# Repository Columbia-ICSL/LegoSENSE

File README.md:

# LegoSENSE
LegoSENSE makes building and deploying sensing systems as easy and as fast as building legos, for **everyone**. LegoSENSE is a software & hardware framework for rapid sensor deployments.

We have provided detailed documentation (and instructional videos soon), for both users, and developers looking to expand the ecosystem.

## Getting Started

For general users, if your system did not come with the software, please flash our prebuilt Raspberry Pi image to the SD card and plug in the hardware.

To develop or build the system from source, please clone this repository using the following git commands. Make sure to pass the `--recurse-submodules` flag to the clone command.

```bash
git clone --recurse-submodules git@github.com:Columbia-ICSL/LegoSENSE.git
```

`/software` contains the source code for LegoSENSE's software system running on Raspberry Pi.

`/hardware` contains all the design resources for developing hardware modules for LegoSENSE, including instructions, hardware references, and design templates.

## Citation

If your academic work has used LegoSENSE, please cite our paper below.

> Minghui Zhao, Stephen Xia, Jingping Nie, Kaiyuan Hou, Avik Dhupar, and Xiaofan Jiang. 2023. LegoSENSE: An Open and Modular Sensing Platform for Rapidly-Deployable IoT Applications. In International Conference on Internet-of-Things Design and Implementation (IoTDI '23), May 09--12, 2023, San Antonio, TX, USA. ACM, New York, NY, USA 14 Pages. [https://doi.org/10.1145/3576842.3582369](https://doi.org/10.1145/3576842.3582369)

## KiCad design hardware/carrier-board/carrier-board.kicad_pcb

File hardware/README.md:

# LegoSENSE Development Guide - Hardware
*This document is written for a hardware developer audience. For information on using LegoSENSE, see [Getting Started](../README.md).*

## Getting Started: hardware design steps

### Step 1: Get Sensor to Work on Breadboard

Acquire a sensor evaluation board (breakout board) and make it work with Raspberry Pi. You may consult the sensor manufacturer for example codes and getting started guides. Once you have the sensor's driver code running on Raspberry Pi and are able to acquire data, you are ready for the next step.

### Step 2: Switch to Module Development Board

In this step, you will move the sensor circuit to a module-like development board that can be plugged into LegoSENSE's carrier board.

There are three module development boards you can use as shown below. On the top half of the board, the 21-Pin connector is broken out for soldering; on the bottom half of the board, type 1 employs a breadboard-style layout, type 2 employs a protoboard-style layout and type 3 includes the common 1.25mm JST connector and 1.0mm I2C connector (STEMMA QT / Qwiic).

| Development Board Type 1                       | Development Board Type 2                       | Development Board Type 3                       |
| ---------------------------------------------- | ---------------------------------------------- | ---------------------------------------------- |
|  |  |  |
|  |  |  |

Choose the one that's most convenient for you to work with, and move the circuit from breadboard to the development board and solder it on there.

Plug the evaluation board into carrier board. Depending on which slot you've plugged in, you will need to change the pin definitions in your sensor driver code to match the pin that the specific carrier board module slot uses. You can consult the table under [Carrier Board Bus Layout](#carrier-board-bus-layout).

Once you get the sensor driver code up running, you are ready for the next step.

### Step 3: Port code into LegoSENSE Framework

In this step, we will port the working sensor driver code into LegoSENSE's framework. Follow [Software Development Guide](../software_dev.md) - once you have the sensor driver running from LegoSENSE's software stack and see the sensor data on the dashboard, you are ready for the final step.

### Step 4: Design and Manufacture Module PCB

In this step, we will create the final version of the sensor module PCB. A template sensor module PCB project is provided in `/hardware/sensor-modules/template`.

| Template Sensor Module PCB (front)                  | Template Sensor Module PCB (back)                   |
| --------------------------------------------------- | --------------------------------------------------- |
|  |  |

1. Duplicating the module template PCB file. This template file is pre-populated with the LegoSENSE standard 21-Pin connector and a EEPROM for auto-recognition of the module. Do not edit this part.
2. Move all the sensor components and peripherials onto the bottom part of the module PCB.
3. Finish the PCB and manufacture it. You could either program the eeprom at manufacturing time and populate it with the ascii string name of the driver, or you can plug in the PCB and use `/software/src/hal/eeprom/write_eep.py` to program the eeprom.

## Project Layout

- `sensor-modules`
  - `template`
  - `<existing_module_names>`
    - `<module_name>.kicad_pro/kicad_sch/kicad_pcb`: KiCad project for the sensor module PCB
    - `jlcpcb`: Folder containing PCB fabrication files. This folder is generated by KiCad plugin [kicad-jlcpcb-tools]( https://github.com/bouni/kicad-jlcpcb-tools).
      - `gerber`: Gerber file for PCB manufacturing
      - `assembly`: Bill of materials (BOM) and parts placement position file for pick-and-place machine (POS)

- `carrier-board`: Carrier board (as a Raspberry Pi shield) PCB design and fabrication files
  - `carrier-board.kicad_pro/kicad_sch/kicad_pcb`: KiCad project for the top-level carrier board PCB
  - `<ADC/eeprom_mux/HeaderToRpi4_overlay1/level_shifter_2ch/sensor_module>.kicad_sch`: Schematics files for submodules in the carrier board PCB project
  - `jlcpcb`: Folder containing PCB fabrication files. This folder is generated by KiCad plugin [kicad-jlcpcb-tools]( https://github.com/bouni/kicad-jlcpcb-tools).
    - `gerber`: Gerber file for PCB manufacturing
    - `assembly`: Bill of materials (BOM) and parts placement position file for pick-and-place machine (POS)
- `module-development-boards`: PCB designs for three different module development boards
- `kicad-library`: Submodule linked to a separate GitHub repository containing the PCB library symbols of the components used in the hardware designs.

### Current List of PCB Design Files

#### Carrier Board PCB

| Carrier Board Front Side             | Carrier Board Back Side              |
| ------------------------------------ | ------------------------------------ |
|  |  |

#### Sensor Modules

| **M1: Temperature, Humidity, Pressure, Wind Speed** | **M2: Ambient Light Color, Light Intensity**                 | **M3: Proximity, Microphone**          | **M4: Motion (IMU)**              |
| --------------------------------------------------- | ------------------------------------------------------------ | -------------------------------------- | --------------------------------- |
|                               |                                        |                  |             |
| **M5: Thermocouple (Temperature)**                  | **M6: Particulate Matter (PM1, PM2.5, PM10); Any I2C Sensor with STEMMA QT / Qwiic** | **M7: CO2, Volatile Organic Compound** | **M8: Gas Density (MQ-X Series)** |
|                               |                                        |                  |             |

## Carrier Board Bus Layout
Note: Raspberry Pi GPIO numbering in this table are BCM (broadcom) pin numbers and is not the physical pin on Raspberry Pi board.

|            | I2C                    | SPI                             | UART (TX, RX)                      | ADC         | GPIO |
| ---------- | ---------------------- | ------------------------------- | ---------------------------------- | ----------- | ---- |
| Module 1   | I2C1 <br/>`/dev/i2c-1` | SPI0, CS0 <br/>`/dev/spidev0.0` | UART1 (14, 15) <br/>`/dev/ttyS0`   | ADC1, CH1-2 | 24   |
| Module 2   | I2C1 <br/>`/dev/i2c-1` | SPI0, CS1 <br/>`/dev/spidev0.1` | UART2 (0, 1) <br/>`/dev/ttyAMA1`   | ADC1, CH3-4 | 25   |
| Module 3   | I2C6 <br/>`/dev/i2c-6` | SPI1, CS0 <br/>`/dev/spidev1.0` | UART3 (4, 5) <br/>`/dev/ttyAMA2`   | ADC2, CH1-2 | 26   |
| Module 4   | I2C6 <br/>`/dev/i2c-6` | SPI1, CS1 <br/>`/dev/spidev1.1` | UART5 (12, 13) <br/>`/dev/ttyAMA3` | ADC2, CH3-4 | 27   |
| ADC1       | I2C1, addr=48          |                                 |                                    |             |      |
| ADC2       | I2C1, addr=49          |                                 |                                    |             |      |
| EEPROM MUX | I2C1, addr=70          |                                 |                                    |             |      |

### Raspberry Pi 4 Device Tree Overlay
```
[spi]
gpio=16,17,18,19,20,21=a4
dtoverlay=spi1-3cs
gpio=7,8,9,10,11=a0
dtoverlay=spi0-2cs

[I2C]
dtoverlay=i2c6

[UART]
enable_uart=1
dtoverlay=uart2
dtoverlay=uart3
dtoverlay=uart5
```

### Raspberry Pi 40-Pin Assignments
| Function   | RPi PCB <br/>Pin# (BCM) | RPi PCB <br/>Pin# (BCM) | Function  |
| ---------- | ----------------------- | ----------------------- | --------- |
| 3V3        | **1** (3V3)             | **2** (5V)              | 5V        |
| I2C1_SDA   | **3** (GPIO 2)          | **4** (5V)              | 5V        |
| I2C1_SCL   | **5** (GPIO 3)          | **6** (GND)             | GND       |
| UART3_TX   | **7** (GPIO 4)          | **8** (GPIO 14)         | UART0_TX  |
| GND        | **9** (GND)             | **10** (GPIO 15)        | UART0_RX  |
| SPI1_CE1   | **11** (GPIO 17)        | **12** (GPIO 18)        | SPI1_CE0  |
| GPIO_M4    | **13** (GPIO 27)        | **14** (GND)            | GND       |
| I2C6_SDA   | **15** (GPIO 22)        | **16** (GPIO 23)        | I2C6_SCL  |
| 3V3        | **17** (3V3)            | **18** (GPIO 24)        | GPIO_M1   |
| SPI0_MOSI  | **19** (GPIO 10)        | **20** (GND)            | GND       |
| SPI0_MISO  | **21** (GPIO 9)         | **22** (GPIO 25)        | GPIO_M2   |
| SPI0_SCK   | **23** (GPIO 11)        | **24** (GPIO 8)         | SPI0_CE0  |
| GND        | **25** (GND)            | **26** (GPIO 7)         | SPI0_CE1  |
| UART2_TX   | **27** (GPIO 0)         | **28** (GPIO 1)         | UART2_RX  |
| UART3_RX   | **29** (GPIO 5)         | **30** (GND)            | GND       |
| *Not Used* | **31** (GPIO 6)         | **32** (GPIO 12)        | UART5_TX  |
| UART5_RX   | **33** (GPIO 13)        | **34** (GND)            | GND       |
| SPI1_MISO  | **35** (GPIO 19)        | **36** (GPIO 16)        | SPI1_CE2  |
| GPIO_M3    | **37** (GPIO 26)        | **38** (GPIO 20)        | SPI1_MOSI |
| GND        | **39** (GND)            | **40** (GPIO 21)        | SPI1_SCK  |

## Module Connector
The universal connector used for all modules and carrier boards is a pair of 21 Pin Mezzanine Connectors shown below.

| Adapter Board Side<br/>21 Pin Mezzanine Connector Receipt | 21 Pin Mezzanine Connector Plug <br/>Sensor Module Side |
| --------------------------------------------------------- | ------------------------------------------------------- |
|        |      |

The layout for the connector is shown below. It includes pins for the common sensor data communication protocols as follows:

- `SCL, SDA`: I2C
- `CS, MOSI, MISO, SCK`: SPI
- `GPIO`: GPIO digital input / output
- `SCL_E, SDA_E`: I2C for EEPROM (used for module auto-recognition and configuration)
- `RX, TX`: UART
- `ADC0, ADC1`: Two analog input channels

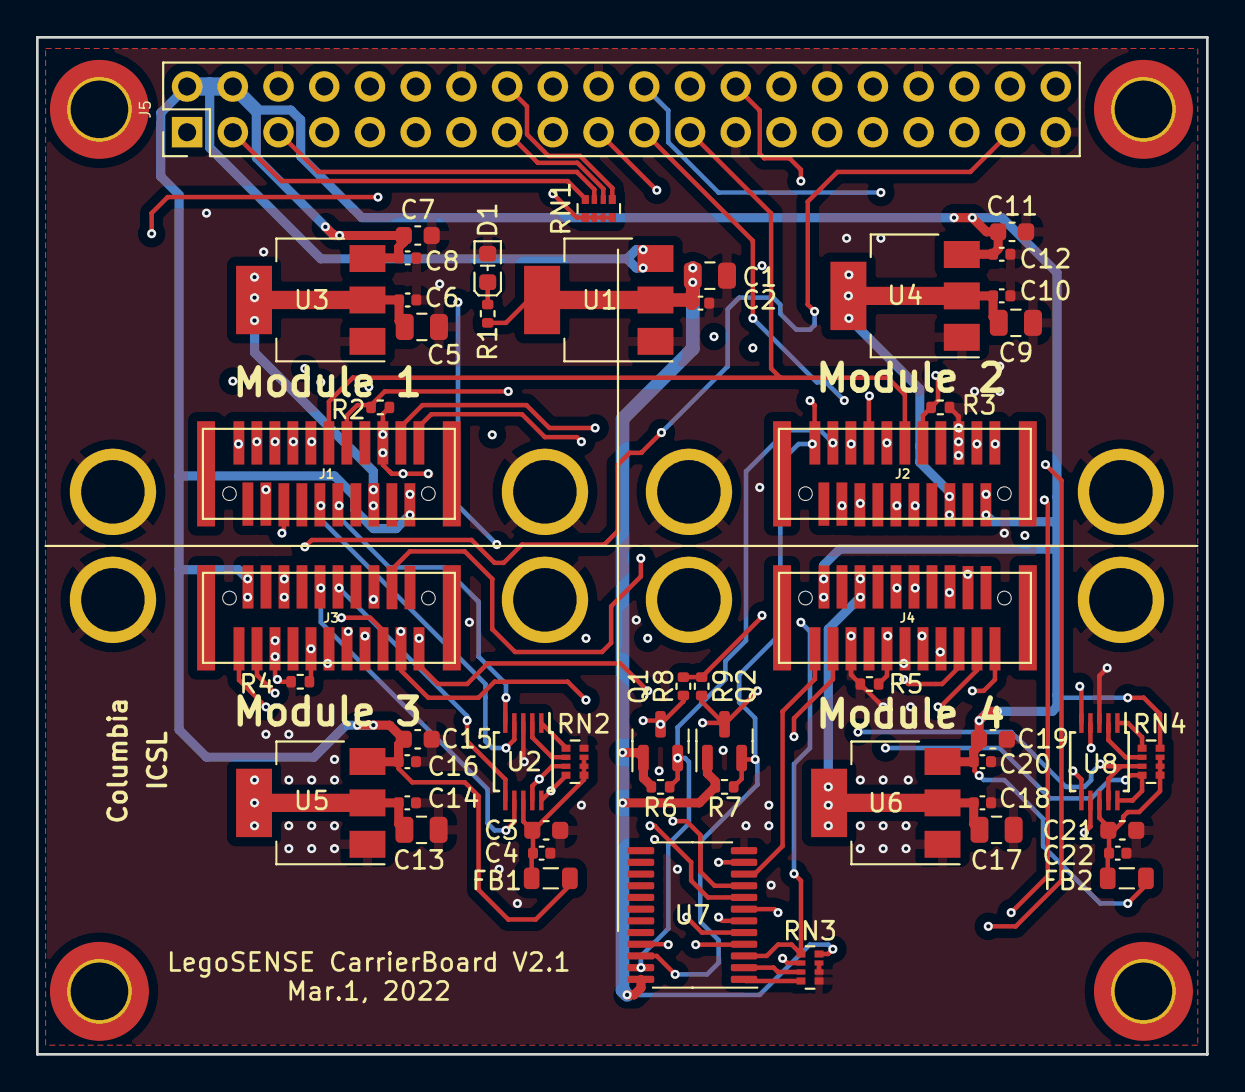
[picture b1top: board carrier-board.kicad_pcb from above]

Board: 4 copper layers, 65.0 x 56.5 mm, 66 parts (0 on the bottom side), 63 nets.

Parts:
C1, C5, C9, C13, C17: C_0805_10uF_25V; C_0805_2012Metric
C2, C4, C6, C10, C14, C18, C22: C_0402_1uF_25V; C_0402_1005Metric
C3, C7, C11, C15, C19, C21: C_0603_4.7uF_16V; C_0603_1608Metric
C8, C12, C16, C20: C_0402_0.1uF_16V; C_0402_1005Metric
D1: LED_0603_Red; LED_0603_1608Metric
FB1, FB2: B_0805_600R; L_0805_2012Metric
H1, H2, H3, H4: MountingHole_Pad; MountingHole_3.2mm_M3_ISO14580_Pad_TopBottom
H5, H6, H7, H8, H9, H10, H11, H12: M1502-B-2545-AL; Spacer_M1502-B-2545_AL
J1, J2, J3, J4: Amphenol_91931-31121_recep; Amphenol_91931_31121LF_RCPT
J5: RPI4_Header; PinHeader_2x20_P2.54mm_Vertical
Q1, Q2: NMOS_BSS138; SOT-23
R1, R2, R3, R4, R5, R6, R7, R8, R9: R_0402_10K; R_0402_1005Metric
RN1, RN2, RN3, RN4: RN_0402x4_10K; R_Array_Convex_4x0402
U1, U3, U4, U5, U6: AMS1117-3.3; SOT-223-3_TabPin2
U2, U8: ADC_ADS1115IDGSR; TSSOP-10_3x3mm_P0.5mm
U7: TCA9548APWR; TSSOP-24_4.4x7.8mm_P0.65mm
U9: ICSL_LOGO; icsl_logo

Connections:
+3V3: C1.1, C2.1, Q1.1 (G), Q2.1 (G), R1.1, R6.1, R7.1, RN3.5 (R4_B), U1.2 (VO), U7.24 (VCC)
/3V_RPi: J5.1, J5.17, RN1.5 (R4_B), RN1.6 (R3_B), RN1.7 (R2_B), RN1.8 (R1_B)
/5V_RPi: C7.1, C8.1, C11.1, C12.1, C15.1, C16.1, C19.1, C20.1, FB1.1, FB2.1, J1.21, J2.21, J3.21, J4.21, J5.2, J5.4, R8.1, R9.1, RN4.1 (R1_T), U1.3 (VI), U3.3 (VI), U4.3 (VI), U5.3 (VI), U6.3 (VI)
/ADC1/VCC_ADC: C3.1, C4.1, FB1.2, RN2.2 (R2_T), RN2.3 (R3_T), RN2.4 (R4_T), U2.8 (VDD)
/ADC2/VCC_ADC: C21.1, C22.1, FB2.2, RN4.2 (R2_T), RN4.3 (R3_T), RN4.4 (R4_T), U8.8 (VDD)
/AN1N: J1.17, U2.5 (AIN1)
/AN1P: J1.16, U2.4 (AIN0)
/AN2N: J2.17, U8.5 (AIN1)
/AN2P: J2.16, U8.4 (AIN0)
/AN3N: J3.17, U2.7 (AIN3)
/AN3P: J3.16, U2.6 (AIN2)
/AN4N: J4.17, U8.7 (AIN3)
/AN4P: J4.16, U8.6 (AIN2)
/GPIO6: J5.31, RN3.4 (R4_T), U7.3 (~RESET)
/GPIO24: J1.5, J5.18, R2.2
/GPIO25: J2.5, J5.22, R3.2
/GPIO26: J3.5, J5.37, R4.2
/GPIO27: J4.5, J5.13, R5.2
/RXD0: J1.13, J5.10
/RXD2: J2.13, J5.28
/RXD3: J3.13, J5.29
/RXD5: J4.13, J5.33
/SCL1: J1.11, J2.11, J5.5, Q2.2 (S), R7.2, RN1.2 (R2_T), U7.22 (SCL)
/SCL1_5V: Q2.3 (D), R9.2, RN2.5 (R4_B), RN4.5 (R4_B), U2.10 (SCL), U8.10 (SCL)
/SCL6: J3.11, J4.11, J5.16, RN1.4 (R4_T)
/SCL_EEPROM1: J1.2, U7.5 (SC0)
/SCL_EEPROM2: J2.2, U7.7 (SC1)
/SCL_EEPROM3: J3.2, U7.9 (SC2)
/SCL_EEPROM4: J4.2, U7.11 (SC3)
/SDA1: J1.10, J2.10, J5.3, Q1.2 (S), R6.2, RN1.1 (R1_T), U7.23 (SDA)
/SDA1_5V: Q1.3 (D), R8.2, RN2.6 (R3_B), RN4.6 (R3_B), U2.9 (SDA), U8.9 (SDA)
/SDA6: J3.10, J4.10, J5.15, RN1.3 (R3_T)
/SDA_EEPROM1: J1.1, U7.4 (SD0)
/SDA_EEPROM2: J2.1, U7.6 (SD1)
/SDA_EEPROM3: J3.1, U7.8 (SD2)
/SDA_EEPROM4: J4.1, U7.10 (SD3)
/SPI0CE0: J1.9, J5.24
/SPI0CE1: J2.9, J5.26
/SPI0MISO: J1.7, J2.7, J5.21
/SPI0MOSI: J1.8, J2.8, J5.19
/SPI0SCLK: J1.6, J2.6, J5.23
/SPI1CE0: J3.9, J5.12
/SPI1CE1: J4.9, J5.11
/SPI1MISO: J3.7, J4.7, J5.35
/SPI1MOSI: J3.8, J4.8, J5.38
/SPI1SCLK: J3.6, J4.6, J5.40
/TXD0: J1.14, J5.8
/TXD2: J2.14, J5.27
/TXD3: J3.14, J5.7
/TXD5: J4.14, J5.32
/module1/3.3V: C5.1, C6.1, J1.19, U3.2 (VO)
/module2/3.3V: C9.1, C10.1, J2.19, U4.2 (VO)
/module3/3.3V: C13.1, C14.1, J3.19, U5.2 (VO)
/module4/3.3V: C17.1, C18.1, J4.19, U6.2 (VO)
GND: C1.2, C2.2, C3.2, C4.2, C5.2, C6.2, C7.2, C8.2, C9.2, C10.2, C11.2, C12.2, C13.2, C14.2, C15.2, C16.2, C17.2, C18.2, C19.2, C20.2, C21.2, C22.2, D1.1 (K), H5.1, H6.1, H7.1, H8.1, H9.1, H10.1, H11.1, H12.1, J1.3, J2.3, J3.3, J4.3, J5.6, J5.9, J5.14, J5.20, J5.25, J5.30, J5.34, J5.39, R2.1, R3.1, R4.1, R5.1, RN2.1 (R1_T), RN3.6 (R3_B), RN3.7 (R2_B), RN3.8 (R1_B), U1.1 (GND), U2.3 (GND), U3.1 (GND), U4.1 (GND), U5.1 (GND), U6.1 (GND), U7.12 (GND), U8.3 (GND)
unnamed: D1.2 (A), R1.2
unnamed: RN2.7 (R2_B), U2.2 (ALERT/RDY)
unnamed: RN2.8 (R1_B), U2.1 (ADDR)
unnamed: RN3.1 (R1_T), U7.1 (A0)
unnamed: RN3.2 (R2_T), U7.2 (A1)
unnamed: RN3.3 (R3_T), U7.21 (A2)
unnamed: RN4.7 (R2_B), U8.2 (ALERT/RDY)
unnamed: RN4.8 (R1_B), U8.1 (ADDR)

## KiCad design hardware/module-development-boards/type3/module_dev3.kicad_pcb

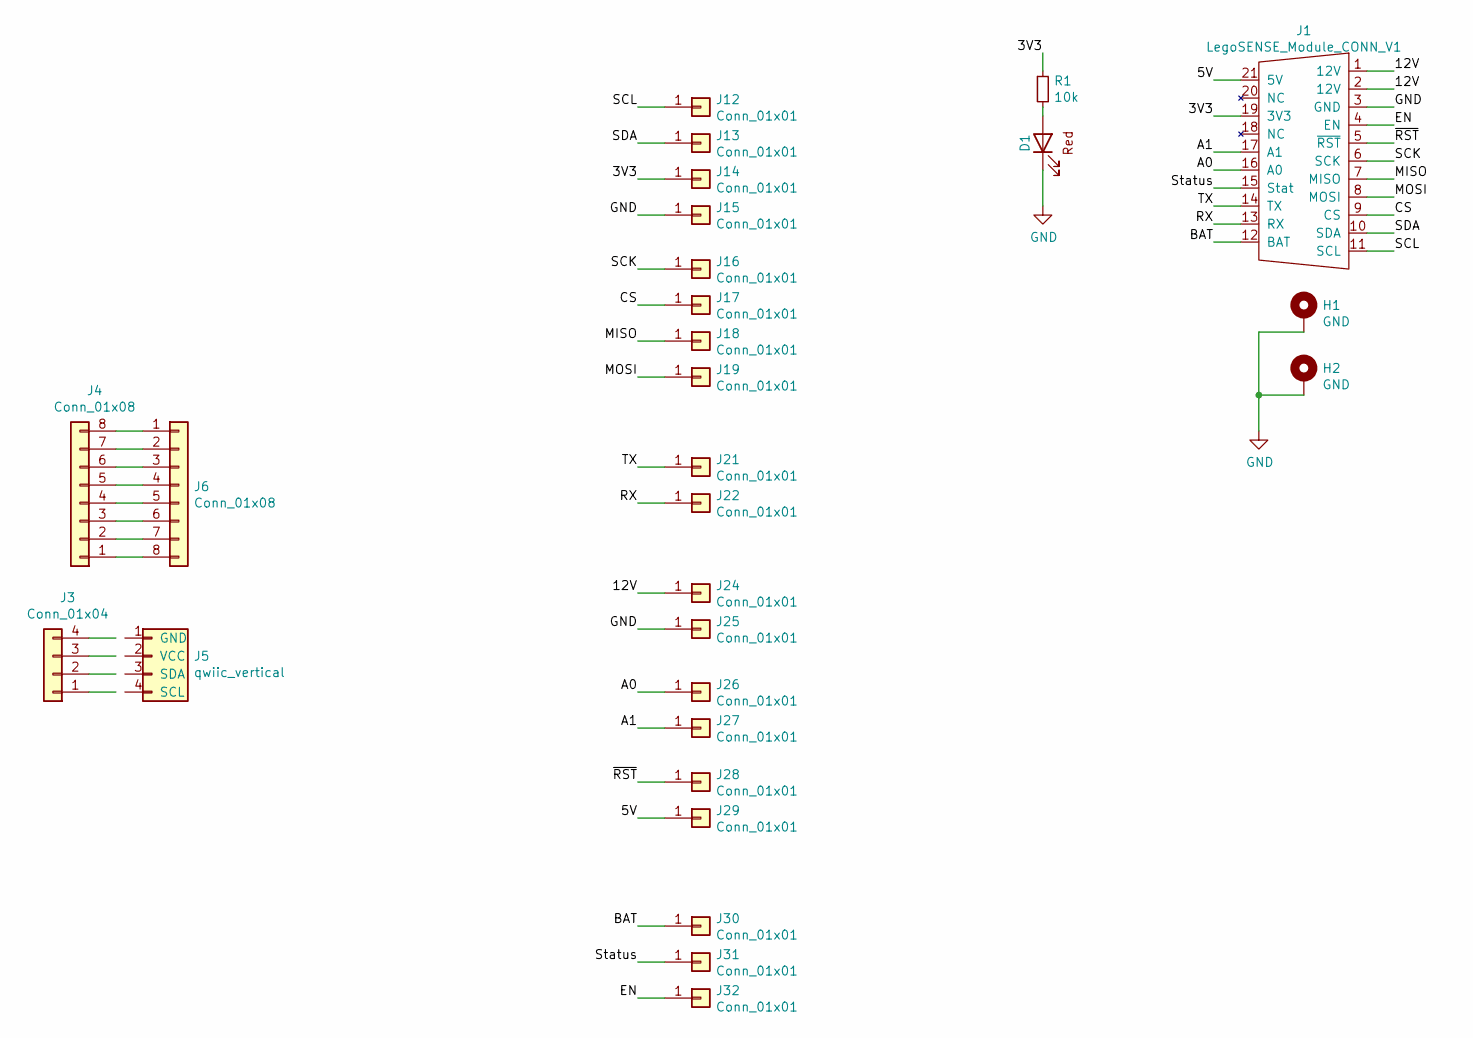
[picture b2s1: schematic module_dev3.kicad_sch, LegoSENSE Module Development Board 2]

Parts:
D1: LED_0603_Red; LED_0603_1608Metric; MFR Part# KT-0603R; LCSC C2286
H1, H2: GND; M1502-B-2545-AL-TOP
J1: LegoSENSE_Module_CONN_V1; Amphenol_91911-31321LF_PLUG
J3: Conn_01x04; PinHeader_1x04_2.54mm_NoSilk
J4: Conn_01x08; PinHeader_1x08_2.54mm_NoSilk
J5: qwiic_vertical; JST_SH_1x04_1.00mm_Vertical
J6: Conn_01x08; JST_GH_BM08B-GHS-TBT_1x08-1MP_P1.25mm_Vertical
J12, J13, J14, J15, J16, J17, J18, J19, J21, J22, J24, J25, J26, J27, J28, J29, J30, J31, J32: Conn_01x01; PinHeader_1x01_NoSilk
R1: 10k; R_0402_1005Metric; LCSC C25744

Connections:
/3V3: J1.19 (3V3), J14.1, R1.1
/5V: J1.21 (5V), J29.1
/12V: J1.1 (12V), J1.2 (12V), J24.1
/A0: J1.16 (A0), J26.1
/A1: J1.17 (A1), J27.1
/BAT: J1.12 (BAT), J30.1
/CS: J1.9 (CS), J17.1
/EN: J1.4 (EN), J32.1
/MISO: J1.7 (MISO), J18.1
/MOSI: J1.8 (MOSI), J19.1
/RX: J1.13 (RX), J22.1
/SCK: J1.6 (SCK), J16.1
/SCL: J1.11 (SCL), J12.1
/SDA: J1.10 (SDA), J13.1
/Status: J1.15 (Stat), J31.1
/TX: J1.14 (TX), J21.1
/~RST: J1.5 (~RST), J28.1
GND: D1.1 (K), H1.1, H2.1, J1.3 (GND), J15.1, J25.1
unnamed: J3.1, J5.4 (SCL)
unnamed: J3.2, J5.3 (SDA)
unnamed: J3.3, J5.2 (VCC)
unnamed: J3.4, J5.1 (GND)
unnamed: J4.1, J6.8
unnamed: J4.2, J6.7
unnamed: J4.3, J6.6
unnamed: J4.4, J6.5
unnamed: J4.5, J6.4
unnamed: J4.6, J6.3
unnamed: J4.7, J6.2
unnamed: J4.8, J6.1

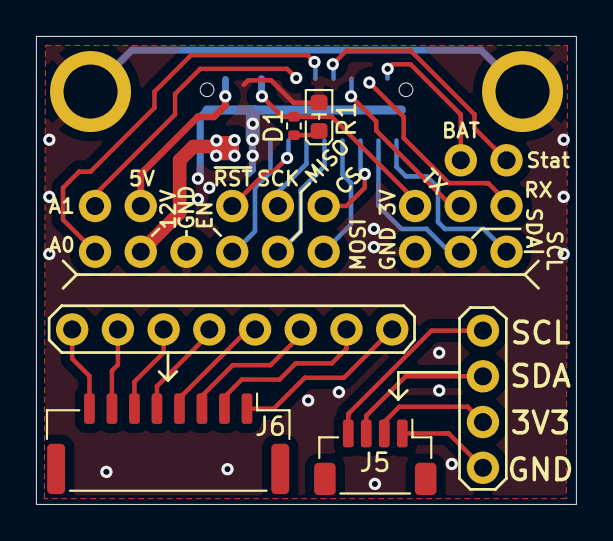
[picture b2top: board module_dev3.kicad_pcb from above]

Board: 2 copper layers, 30.0 x 26.0 mm, 28 parts (1 on the bottom side), 30 nets.

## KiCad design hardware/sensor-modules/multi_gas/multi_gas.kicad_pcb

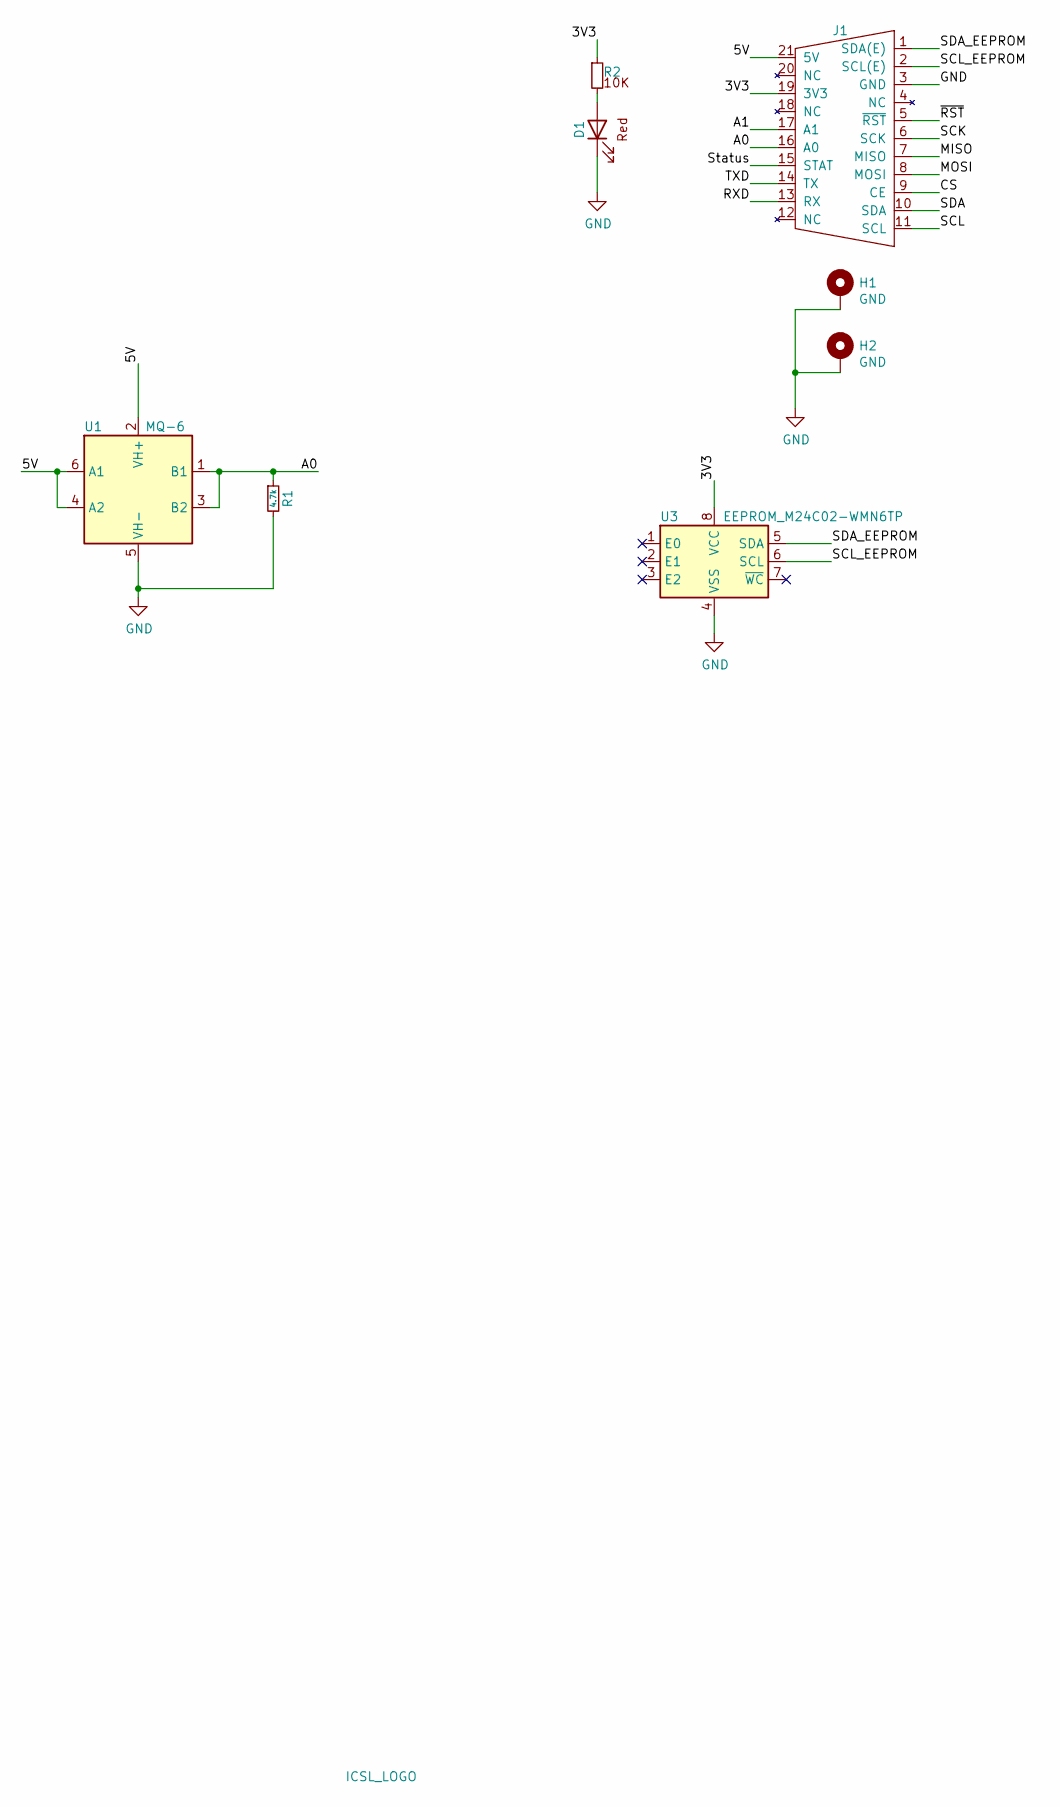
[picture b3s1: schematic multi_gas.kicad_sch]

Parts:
D1: LED_0603_Red; LED_0603_1608Metric; MFR Part# KT-0603R; LCSC C2286
H1, H2: GND; M1502-B-2545-AL-TOP
J1: Amphenol_91911-31321_plug; Amphenol_91911-31321LF_PLUG; LCSC C9900009023
R1: 4.7k; R_1206_3216Metric; LCSC C17936
R2: R_0402_10K; R_0402_1005Metric; MFR Part# 0402WGF1002TCE; LCSC C25744
U1: MQ-6
U2: ICSL_LOGO; icsl_logo
U3: EEPROM_M24C02-WMN6TP; SOIC-8_3.9x4.9mm_P1.27mm; MFR Part# M24C02-WMN6TP; LCSC C7562

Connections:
/3V3: J1.19 (3V3), R2.1, U3.8 (VCC)
/5V: J1.21 (5V), U1.2 (VH+), U1.4 (A2), U1.6 (A1)
/A0: J1.16 (A0), R1.1, U1.1 (B1), U1.3 (B2)
/A1: J1.17 (A1)
/CS: J1.9 (CE)
/MISO: J1.7 (MISO)
/MOSI: J1.8 (MOSI)
/RXD: J1.13 (RX)
/SCK: J1.6 (SCK)
/SCL: J1.11 (SCL)
/SCL_EEPROM: J1.2 (SCL(E)), U3.6 (SCL)
/SDA: J1.10 (SDA)
/SDA_EEPROM: J1.1 (SDA(E)), U3.5 (SDA)
/Status: J1.15 (STAT)
/TXD: J1.14 (TX)
/~RST: J1.5 (~RST)
GND: D1.1 (K), H1.1, H2.1, J1.3 (GND), R1.2, U1.5 (VH-), U3.4 (VSS)
unnamed: D1.2 (A), R2.2

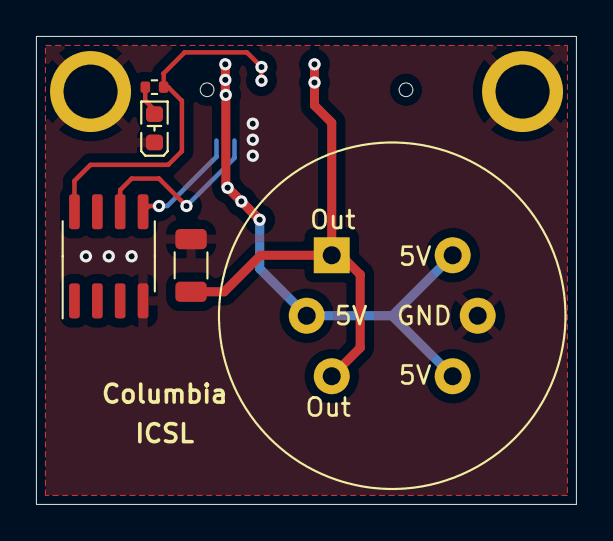
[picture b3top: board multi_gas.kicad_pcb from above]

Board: 4 copper layers, 30.0 x 26.0 mm, 9 parts (1 on the bottom side), 7 nets.

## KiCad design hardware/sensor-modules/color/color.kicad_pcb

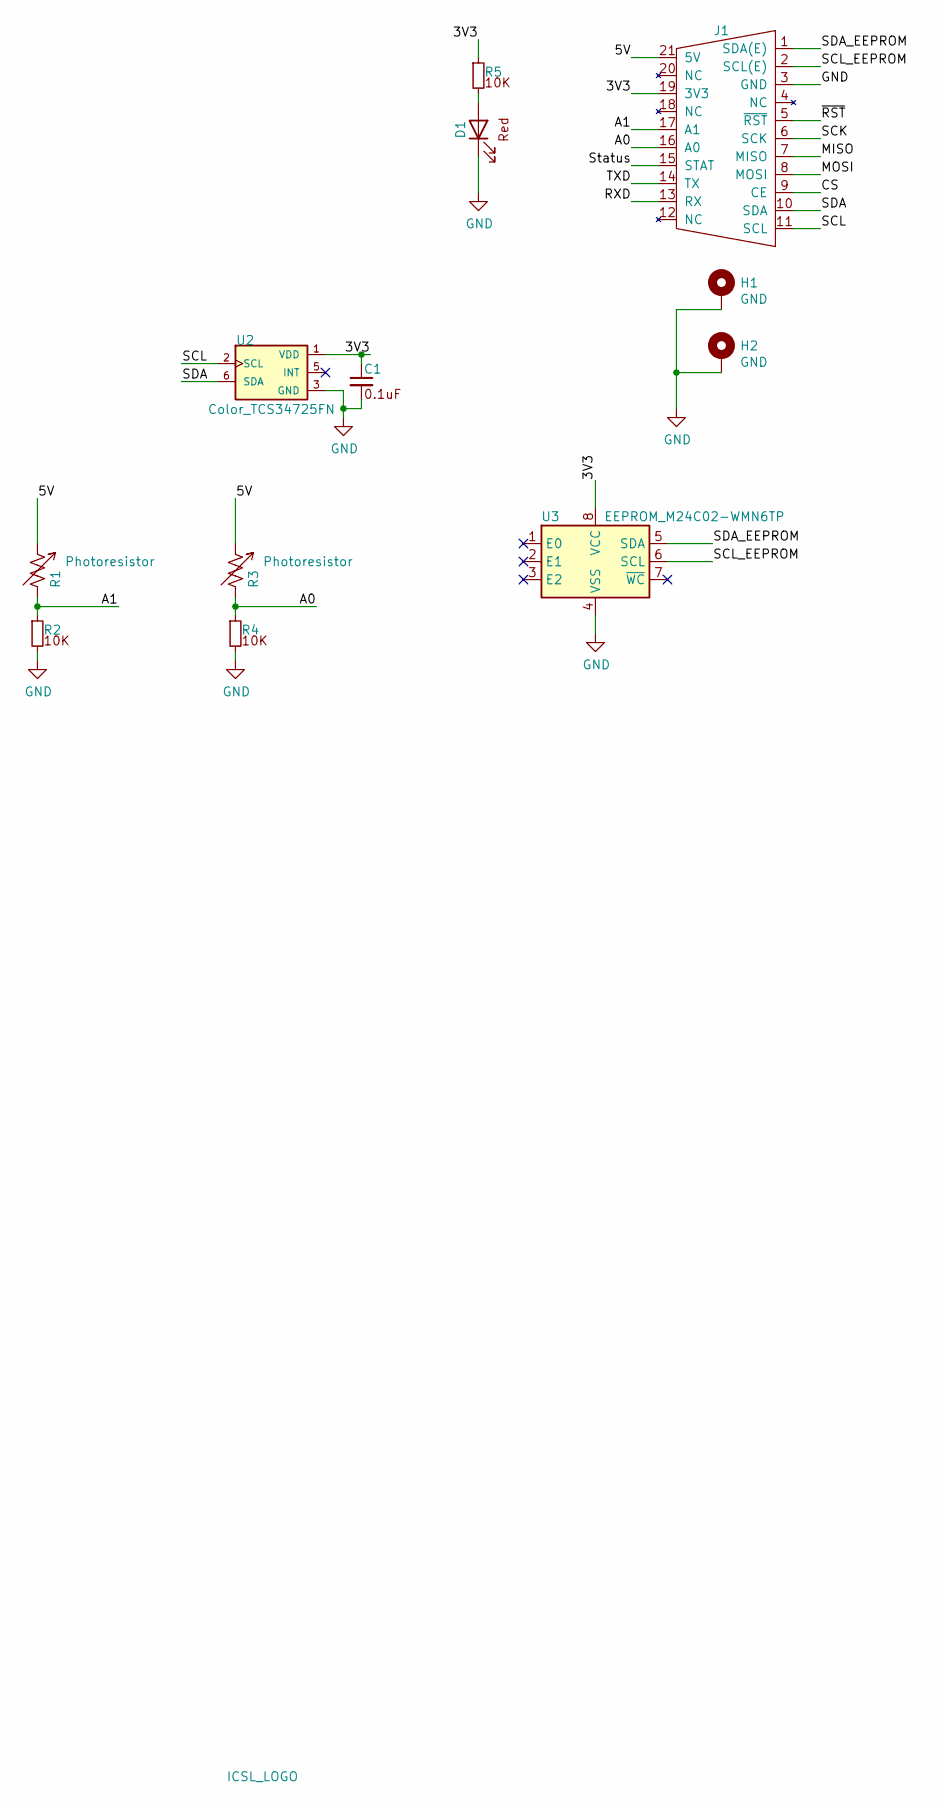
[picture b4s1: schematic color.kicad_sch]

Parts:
C1: C_0402_0.1uF_16V; C_0402_1005Metric; MFR Part# CL05B104KO5NNNC; LCSC C1525
D1: LED_0603_Red; LED_0603_1608Metric; MFR Part# KT-0603R; LCSC C2286
H1, H2: GND; M1502-B-2545-AL-TOP
J1: Amphenol_91911-31321_plug; Amphenol_91911-31321LF_PLUG; LCSC C9900009023
R1, R3: Photoresistor; R_LDR_5.0x4.1mm_P3mm_Vertical
R2, R4, R5: R_0402_10K; R_0402_1005Metric; MFR Part# 0402WGF1002TCE; LCSC C25744
U1: ICSL_LOGO; icsl_logo
U2: Color_TCS34725FN; TCS34725FN; MFR Part# TCS34725FN; LCSC C2649487
U3: EEPROM_M24C02-WMN6TP; SOIC-8_3.9x4.9mm_P1.27mm; MFR Part# M24C02-WMN6TP; LCSC C7562

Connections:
/3V3: C1.1, J1.19 (3V3), R5.1, U2.1 (VDD), U3.8 (VCC)
/5V: J1.21 (5V), R1.1, R3.1
/A0: J1.16 (A0), R3.2, R4.1
/A1: J1.17 (A1), R1.2, R2.1
/CS: J1.9 (CE)
/MISO: J1.7 (MISO)
/MOSI: J1.8 (MOSI)
/RXD: J1.13 (RX)
/SCK: J1.6 (SCK)
/SCL: J1.11 (SCL), U2.2 (SCL)
/SCL_EEPROM: J1.2 (SCL(E)), U3.6 (SCL)
/SDA: J1.10 (SDA), U2.6 (SDA)
/SDA_EEPROM: J1.1 (SDA(E)), U3.5 (SDA)
/Status: J1.15 (STAT)
/TXD: J1.14 (TX)
/~RST: J1.5 (~RST)
GND: C1.2, D1.1 (K), H1.1, H2.1, J1.3 (GND), R2.2, R4.2, U2.3 (GND), U3.4 (VSS)
unnamed: D1.2 (A), R5.2

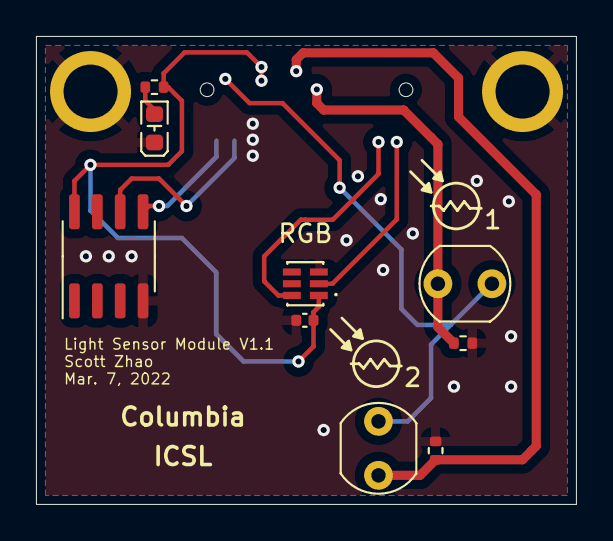
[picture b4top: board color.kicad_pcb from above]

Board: 4 copper layers, 30.0 x 26.0 mm, 13 parts (1 on the bottom side), 10 nets.

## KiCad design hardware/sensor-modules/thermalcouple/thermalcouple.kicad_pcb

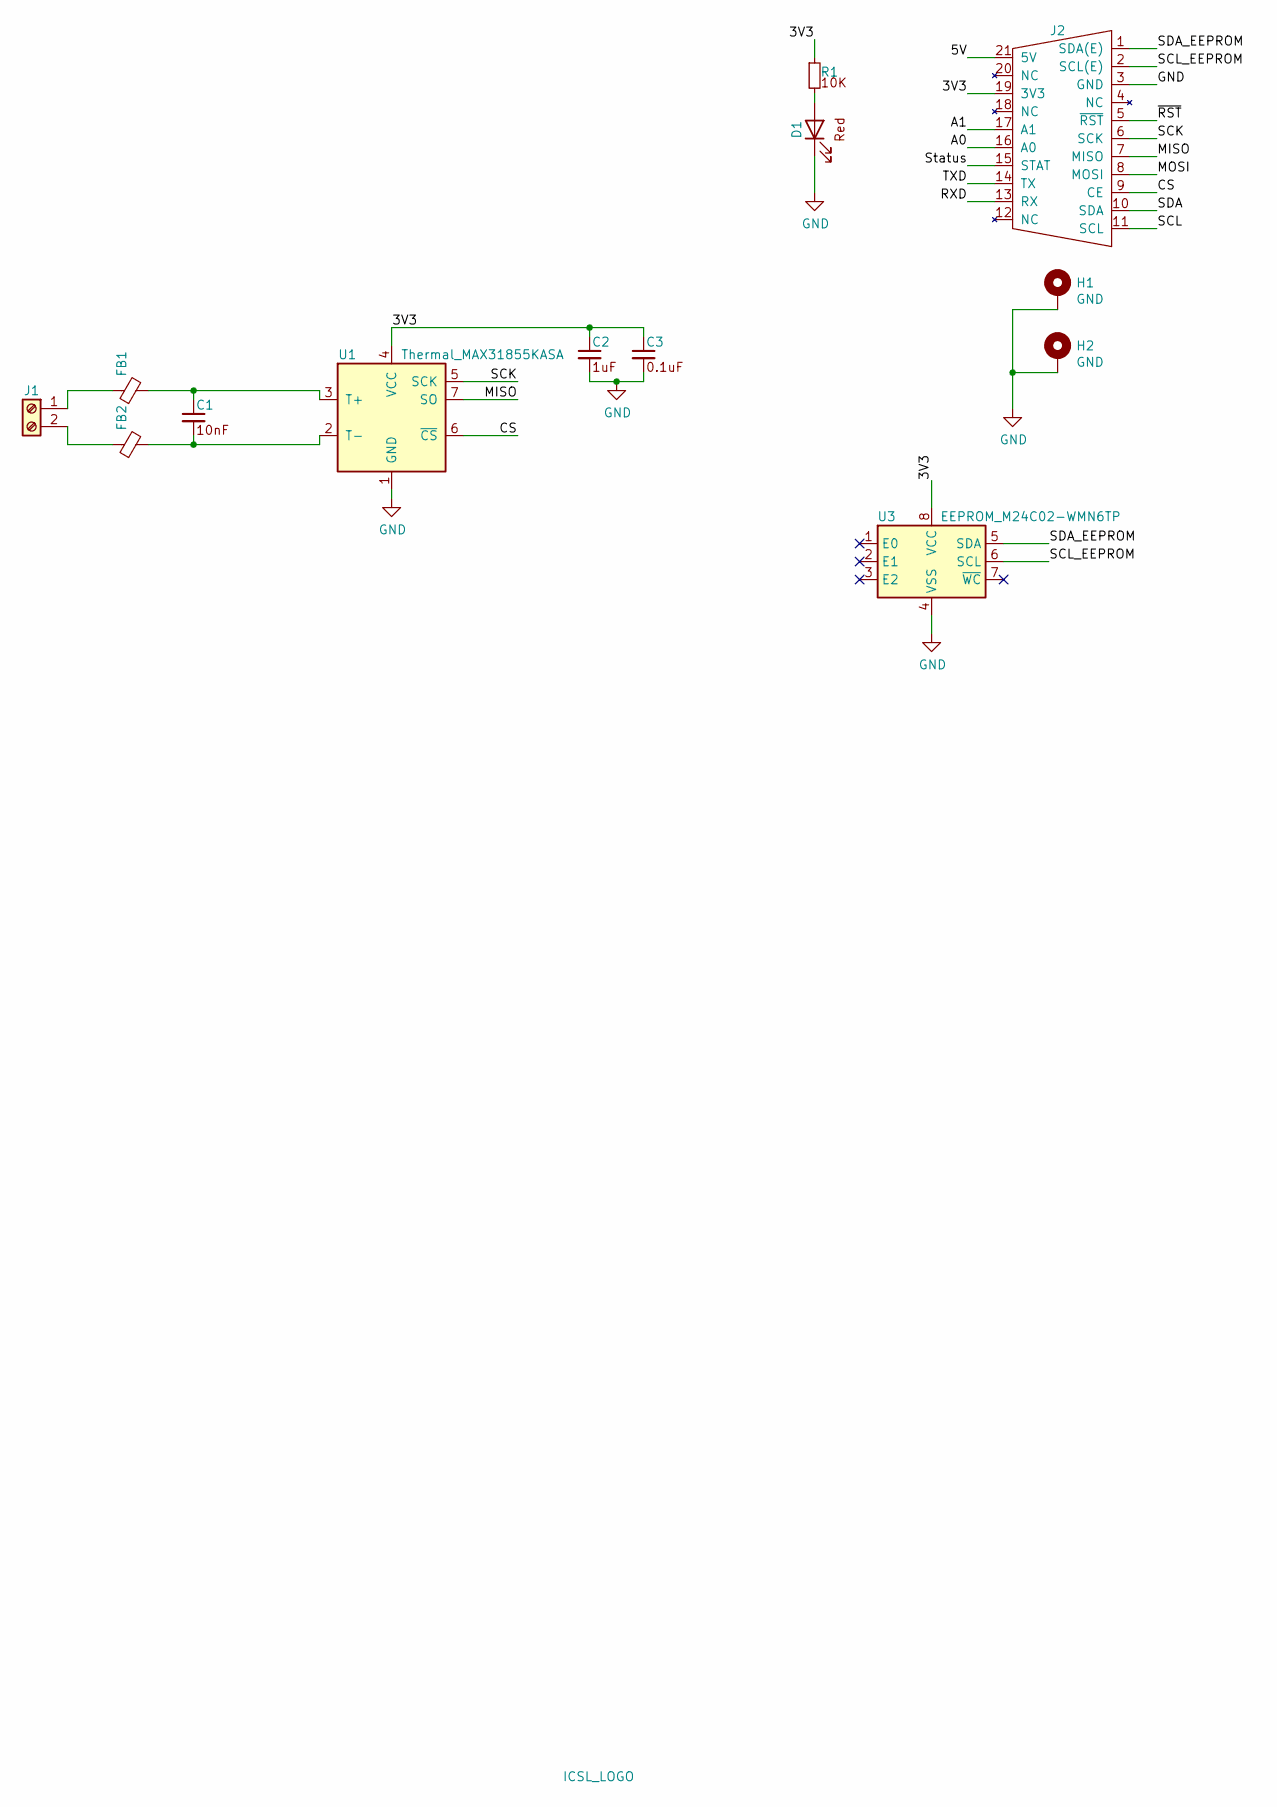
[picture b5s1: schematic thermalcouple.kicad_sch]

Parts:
C1: C_0805_10nF_50V; C_0805_2012Metric; MFR Part# CL21B103KBANNNC; LCSC C1710
C2: C_0402_1uF_25V; C_0402_1005Metric; MFR Part# CL05A105KA5NQNC; LCSC C52923
C3: C_0402_0.1uF_16V; C_0402_1005Metric; MFR Part# CL05B104KO5NNNC; LCSC C1525
D1: LED_0603_Red; LED_0603_1608Metric; MFR Part# KT-0603R; LCSC C2286
FB1, FB2: B_0805_600R; L_0805_2012Metric; MFR Part# GZ2012D601TF; LCSC C1017
H1, H2: GND; M1502-B-2545-AL-TOP
J1: Screw_Terminal_01x02_3.5mm_horiz; TerminalBlock_1x02_P3.50mm_Horizontal; MFR Part# KF350-3.5-2P; LCSC C474892
J2: Amphenol_91911-31321_plug; Amphenol_91911-31321LF_PLUG; LCSC C9900009023
R1: R_0402_10K; R_0402_1005Metric; MFR Part# 0402WGF1002TCE; LCSC C25744
U1: Thermal_MAX31855KASA; SOIC-8_3.9x4.9mm_P1.27mm; MFR Part# MAX31855KASA+T; LCSC C52028
U2: ICSL_LOGO; icsl_logo
U3: EEPROM_M24C02-WMN6TP; SOIC-8_3.9x4.9mm_P1.27mm; MFR Part# M24C02-WMN6TP; LCSC C7562

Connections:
/3V3: C2.1, C3.1, J2.19 (3V3), R1.1, U1.4 (VCC), U3.8 (VCC)
/5V: J2.21 (5V)
/A0: J2.16 (A0)
/A1: J2.17 (A1)
/CS: J2.9 (CE), U1.6 (~CS)
/MISO: J2.7 (MISO), U1.7 (SO)
/MOSI: J2.8 (MOSI)
/RXD: J2.13 (RX)
/SCK: J2.6 (SCK), U1.5 (SCK)
/SCL: J2.11 (SCL)
/SCL_EEPROM: J2.2 (SCL(E)), U3.6 (SCL)
/SDA: J2.10 (SDA)
/SDA_EEPROM: J2.1 (SDA(E)), U3.5 (SDA)
/Status: J2.15 (STAT)
/TXD: J2.14 (TX)
/~RST: J2.5 (~RST)
GND: C2.2, C3.2, D1.1 (K), H1.1, H2.1, J2.3 (GND), U1.1 (GND), U3.4 (VSS)
unnamed: C1.1, FB1.2, U1.3 (T+)
unnamed: C1.2, FB2.2, U1.2 (T-)
unnamed: D1.2 (A), R1.2
unnamed: FB1.1, J1.1
unnamed: FB2.1, J1.2

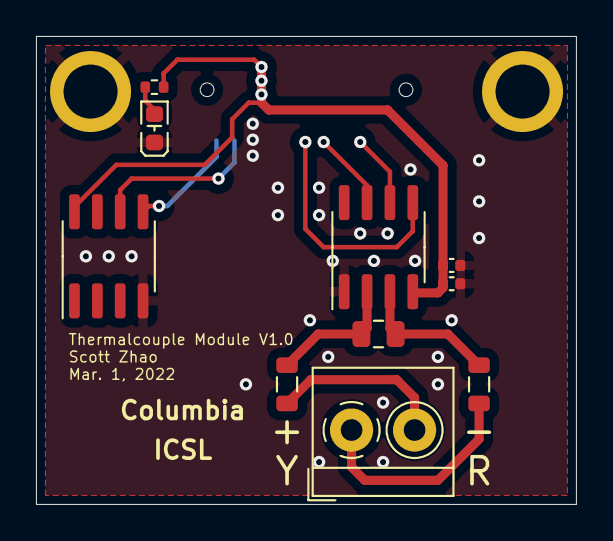
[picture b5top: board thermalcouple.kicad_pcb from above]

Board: 4 copper layers, 30.0 x 26.0 mm, 14 parts (1 on the bottom side), 12 nets.

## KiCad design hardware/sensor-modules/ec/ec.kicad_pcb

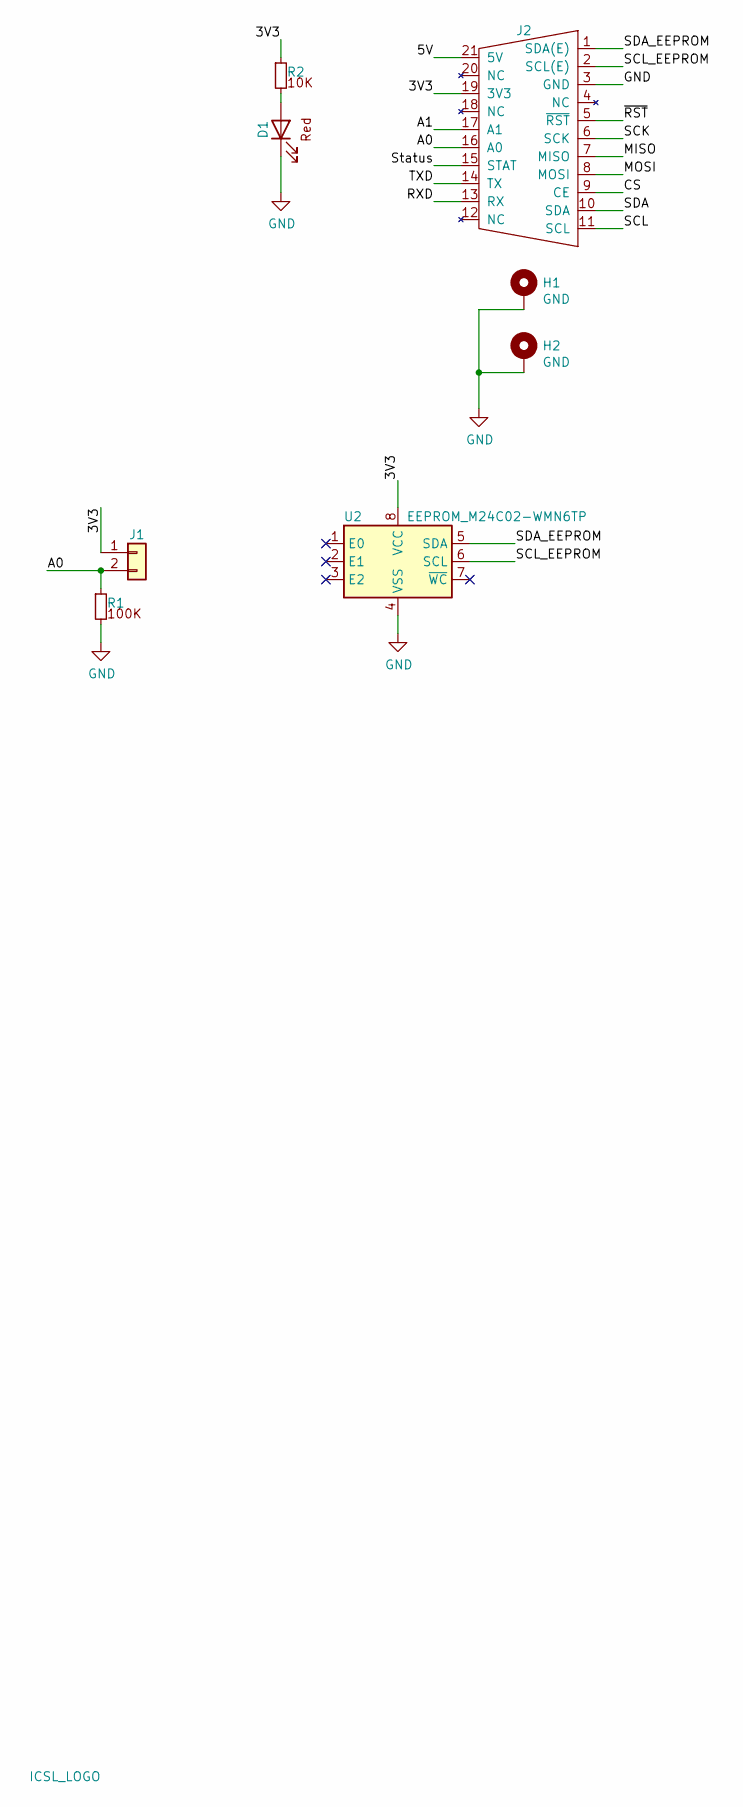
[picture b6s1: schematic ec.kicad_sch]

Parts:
D1: LED_0603_Red; LED_0603_1608Metric; MFR Part# KT-0603R; LCSC C2286
H1, H2: GND; M1502-B-2545-AL-TOP
J1: DC-2.1MM; DC-060A; MFR Part# DC-060A; LCSC C129005
J2: Amphenol_91911-31321_plug; Amphenol_91911-31321LF_PLUG; LCSC C9900009023
R1: R_0402_100K; R_0402_1005Metric; MFR Part# 0402WGF1003TCE; LCSC C25741
R2: R_0402_10K; R_0402_1005Metric; MFR Part# 0402WGF1002TCE; LCSC C25744
U1: ICSL_LOGO; icsl_logo
U2: EEPROM_M24C02-WMN6TP; SOIC-8_3.9x4.9mm_P1.27mm; MFR Part# M24C02-WMN6TP; LCSC C7562

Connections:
/3V3: J1.1, J2.19 (3V3), R2.1, U2.8 (VCC)
/5V: J2.21 (5V)
/A0: J1.2, J2.16 (A0), R1.1
/A1: J2.17 (A1)
/CS: J2.9 (CE)
/MISO: J2.7 (MISO)
/MOSI: J2.8 (MOSI)
/RXD: J2.13 (RX)
/SCK: J2.6 (SCK)
/SCL: J2.11 (SCL)
/SCL_EEPROM: J2.2 (SCL(E)), U2.6 (SCL)
/SDA: J2.10 (SDA)
/SDA_EEPROM: J2.1 (SDA(E)), U2.5 (SDA)
/Status: J2.15 (STAT)
/TXD: J2.14 (TX)
/~RST: J2.5 (~RST)
GND: D1.1 (K), H1.1, H2.1, J2.3 (GND), R1.2, U2.4 (VSS)
unnamed: D1.2 (A), R2.2

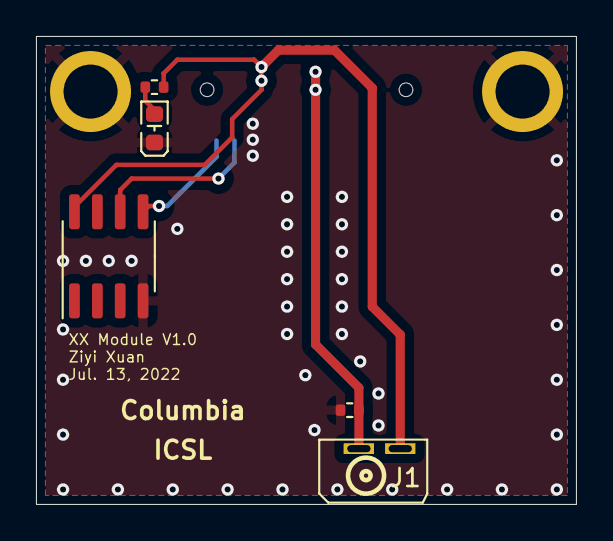
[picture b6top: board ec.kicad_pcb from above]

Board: 4 copper layers, 30.0 x 26.0 mm, 9 parts (1 on the bottom side), 6 nets.
